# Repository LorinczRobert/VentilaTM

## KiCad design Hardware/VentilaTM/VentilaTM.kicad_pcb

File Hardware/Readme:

Still a work in progress, please review

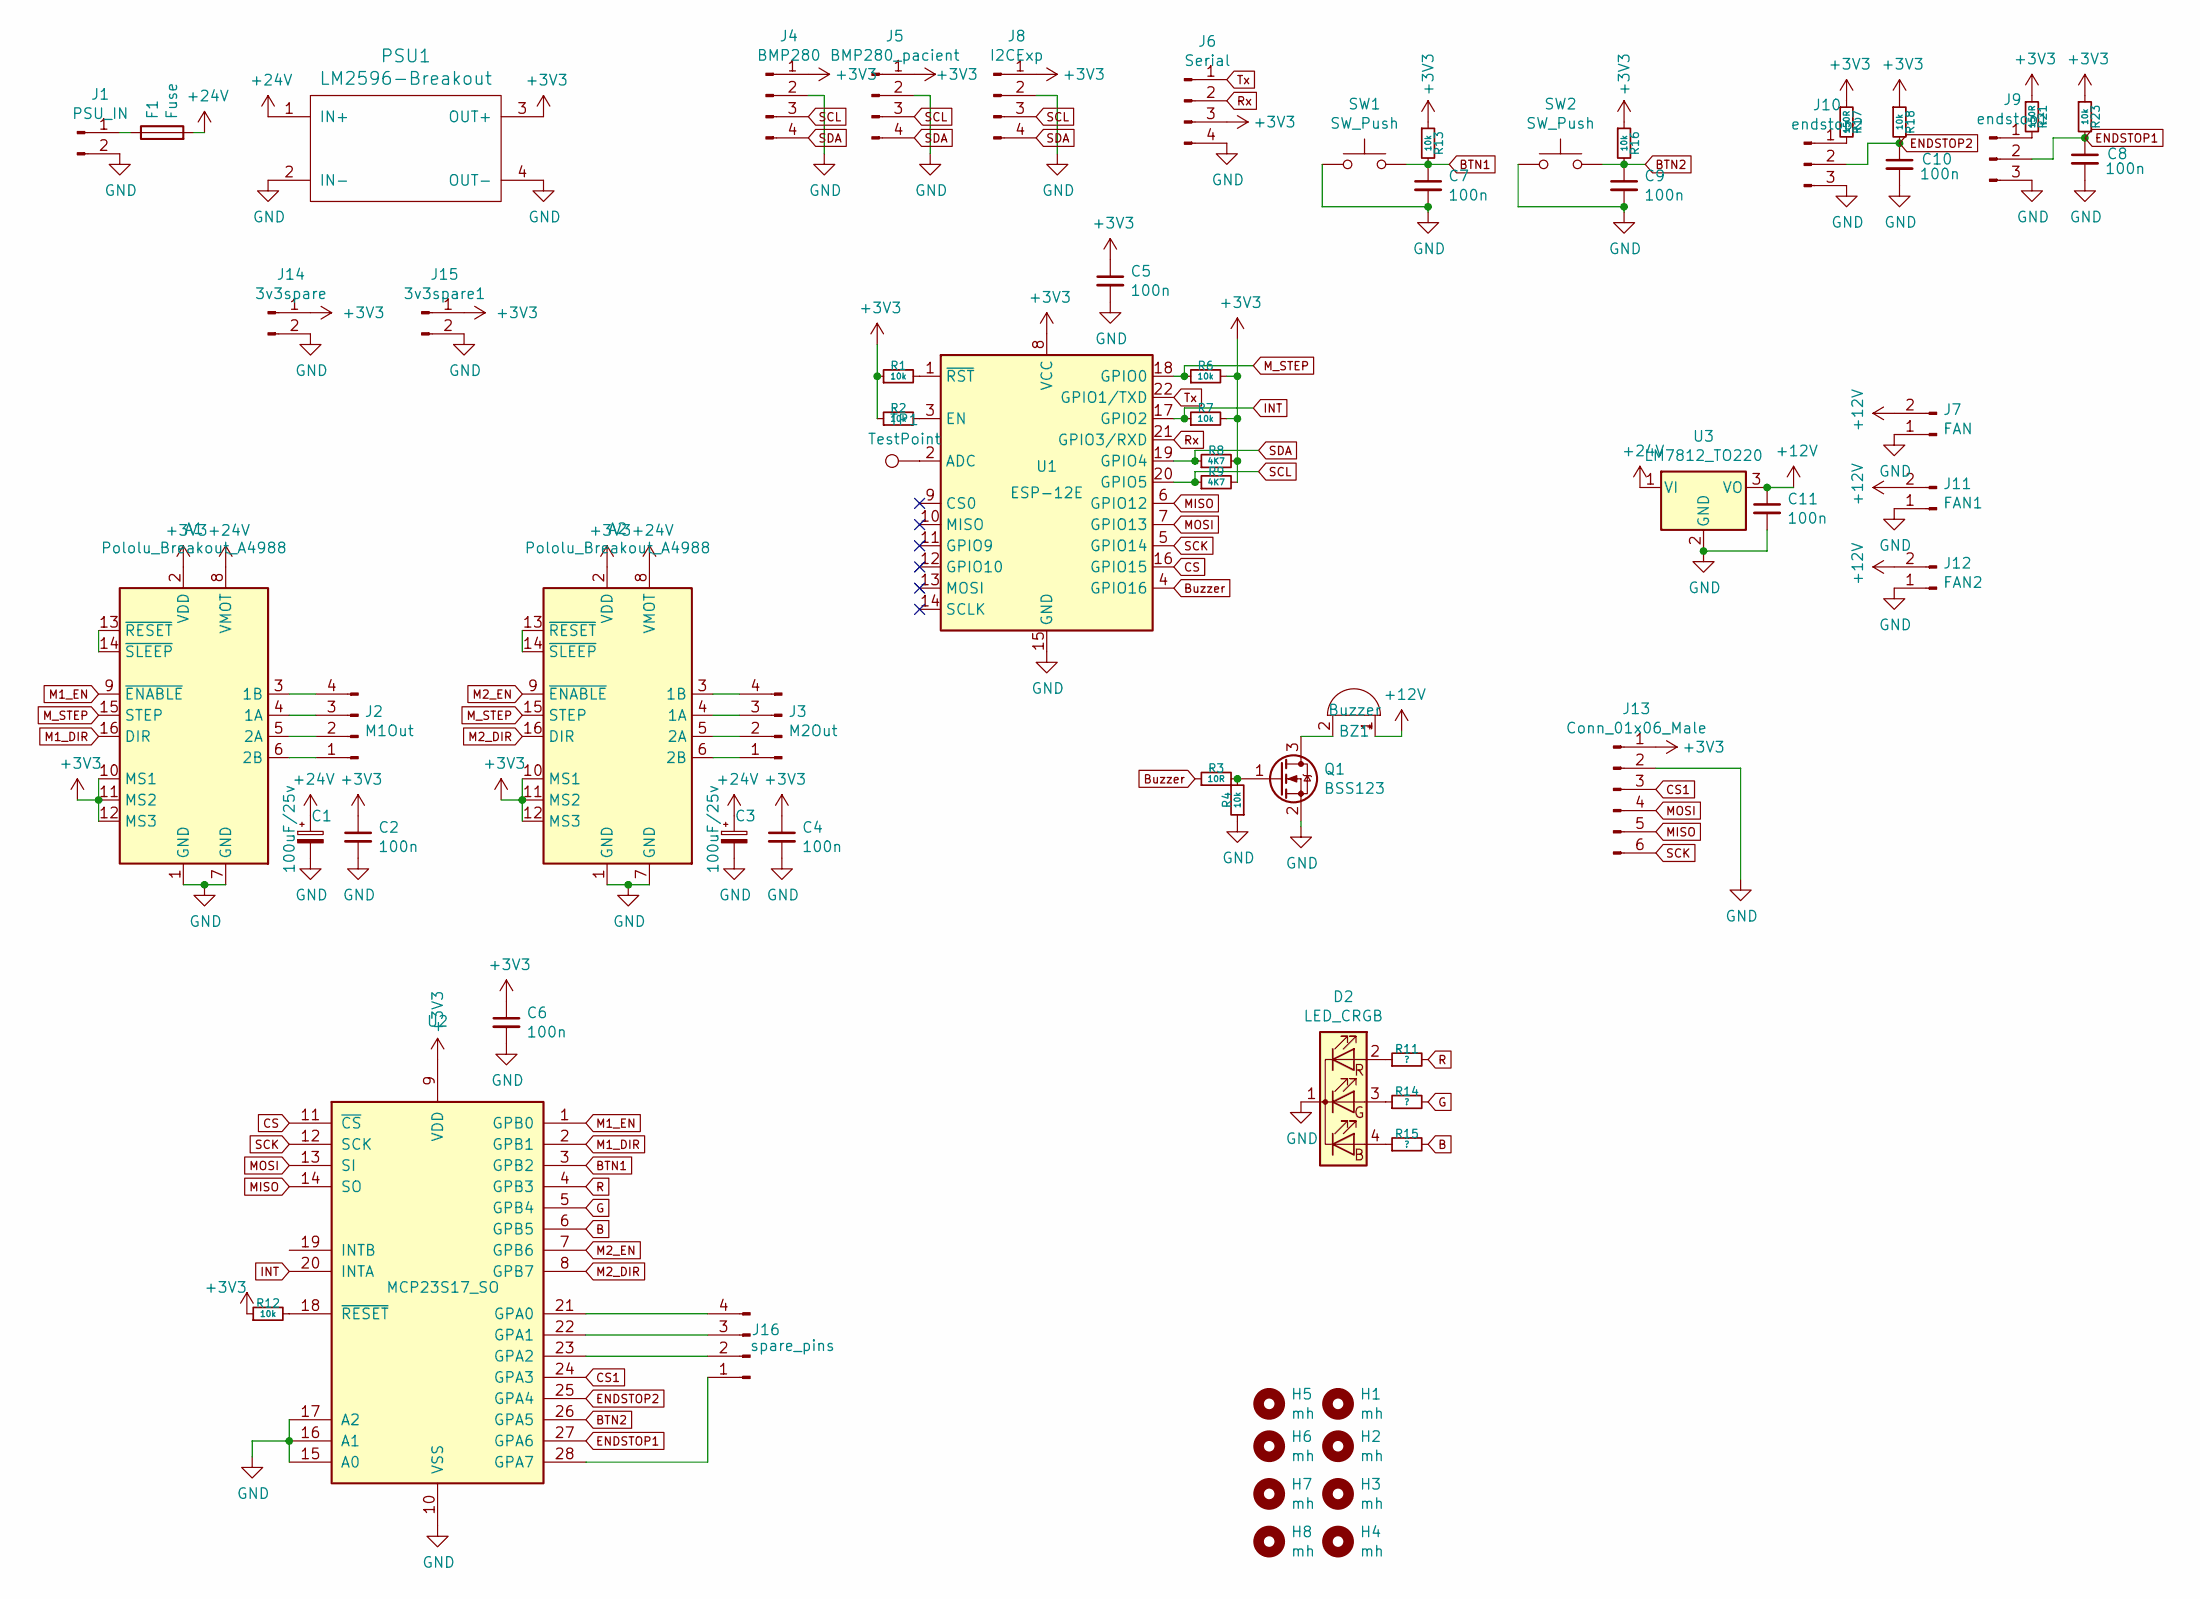
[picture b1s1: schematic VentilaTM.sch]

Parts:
A1, A2: Pololu_Breakout_A4988; Pololu_Breakout-16_15.2x20.3mm
BZ1: Buzzer; Buzzer_12x9.5RM7.6
C1, C3: 100uF/25v; CP_Elec_6.3x7.7
C2, C4, C5, C6, C7, C8, C9, C10, C11: 100n; C_0805_2012Metric_Pad1.15x1.40mm_HandSolder
D2: LED_CRGB; LED_D5.0mm-4_RGB_Wide_Pins
F1: Fuse; Fuse_BelFuse_0ZRE0100FF_L18.7mm_W5.1mm
H1, H2, H3, H4, H5, H6, H7, H8: mh; MountingHole_3.2mm_M3
J1: PSU_IN; TerminalBlock_bornier-2_P5.08mm
J2: M1Out; PinHeader_1x04_P2.54mm_Vertical
J3: M2Out; PinHeader_1x04_P2.54mm_Vertical
J4: BMP280; PinHeader_1x04_P2.54mm_Vertical
J5: BMP280_pacient; PinHeader_1x04_P2.54mm_Vertical
J6: Serial; PinHeader_1x04_P2.54mm_Vertical
J7: FAN; PinHeader_1x02_P2.54mm_Vertical
J8: I2CExp; PinHeader_1x04_P2.54mm_Vertical
J9: endstop1; PinHeader_1x03_P2.54mm_Vertical
J10: endstop2; PinHeader_1x03_P2.54mm_Vertical
J11: FAN1; PinHeader_1x02_P2.54mm_Vertical
J12: FAN2; PinHeader_1x02_P2.54mm_Vertical
J13: Conn_01x06_Male; PinHeader_1x06_P2.54mm_Vertical
J14: 3v3spare; PinHeader_1x02_P2.54mm_Vertical
J15: 3v3spare1; PinHeader_1x02_P2.54mm_Vertical
J16: spare_pins; PinHeader_1x04_P2.54mm_Vertical
PSU1: LM2596-Breakout; LM2596-breakout_board
Q1: BSS123; SOT-23
R1, R2, R4, R6, R7, R12, R13, R16, R18, R23: 10k; R_0805_2012Metric_Pad1.15x1.40mm_HandSolder
R3: 10R; R_0805_2012Metric_Pad1.15x1.40mm_HandSolder
R8, R9: 4K7; R_0805_2012Metric_Pad1.15x1.40mm_HandSolder
R11, R14, R15: ?; R_0805_2012Metric_Pad1.15x1.40mm_HandSolder
R17, R21: 150R; R_0805_2012Metric_Pad1.15x1.40mm_HandSolder
SW1, SW2: SW_Push; SW_PUSH_6mm_H7.3mm
TP1: TestPoint; TestPoint_Pad_D1.5mm
U1: ESP-12E
U2: MCP23S17_SO; SOIC-28W_7.5x17.9mm_P1.27mm
U3: LM7812_TO220; TO-220-3_Horizontal_TabUp

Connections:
+3V3: A1.2 (VDD), A1.10 (MS1), A1.11 (MS2), A1.12 (MS3), A2.2 (VDD), A2.10 (MS1), A2.11 (MS2), A2.12 (MS3), C2.1, C4.1, C5.1, C6.1, J4.1, J5.1, J6.3, J8.1, J13.1, J14.1, J15.1, PSU1.3 (OUT+), R1.1, R2.1, R6.2, R7.2, R8.2, R9.2, R12.1, R13.1, R16.1, R17.1, R18.1, R21.1, R23.1, U1.8 (VCC), U2.9 (VDD)
+12V: BZ1.1 (-), C11.1, J7.2, J11.2, J12.2, U3.3 (VO)
+24V: A1.8 (VMOT), A2.8 (VMOT), C1.1, C3.1, F1.2, PSU1.1 (IN+), U3.1 (VI)
B: R15.2, U2.6 (GPB5)
BTN1: C7.1, R13.2, SW1.2, U2.3 (GPB2)
BTN2: C9.1, R16.2, SW2.2, U2.26 (GPA5)
Buzzer: R3.1, U1.4 (GPIO16)
CS: U1.16 (GPIO15), U2.11 (~CS~)
CS1: J13.3, U2.24 (GPA3)
ENDSTOP1: C8.1, J9.2, R23.2, U2.27 (GPA6)
ENDSTOP2: C10.1, J10.2, R18.2, U2.25 (GPA4)
G: R14.2, U2.5 (GPB4)
GND: A1.1 (GND), A1.7 (GND), A2.1 (GND), A2.7 (GND), C1.2, C2.2, C3.2, C4.2, C5.2, C6.2, C7.2, C8.2, C9.2, C10.2, C11.2, D2.1 (K), J1.2, J4.2, J5.2, J6.4, J7.1, J8.2, J9.3, J10.3, J11.1, J12.1, J13.2, J14.2, J15.2, PSU1.2 (IN-), PSU1.4 (OUT-), Q1.2 (S), R4.1, SW1.1, SW2.1, U1.15 (GND), U2.10 (VSS), U2.15 (A0), U2.16 (A1), U2.17 (A2), U3.2 (GND)
INT: R7.1, U1.17 (GPIO2), U2.20 (INTA)
M1_DIR: A1.16 (DIR), U2.2 (GPB1)
M1_EN: A1.9 (~ENABLE), U2.1 (GPB0)
M2_DIR: A2.16 (DIR), U2.8 (GPB7)
M2_EN: A2.9 (~ENABLE), U2.7 (GPB6)
MISO: J13.5, U1.6 (GPIO12), U2.14 (SO)
MOSI: J13.4, U1.7 (GPIO13), U2.13 (SI)
M_STEP: A1.15 (STEP), A2.15 (STEP), R6.1, U1.18 (GPIO0)
unnamed: A1.3 (1B), J2.4
unnamed: A1.4 (1A), J2.3
unnamed: A1.5 (2A), J2.2
unnamed: A1.6 (2B), J2.1
unnamed: A1.13 (~RESET), A1.14 (~SLEEP)
unnamed: A2.3 (1B), J3.4
unnamed: A2.4 (1A), J3.3
unnamed: A2.5 (2A), J3.2
unnamed: A2.6 (2B), J3.1
unnamed: A2.13 (~RESET), A2.14 (~SLEEP)
unnamed: BZ1.2 (+), Q1.3 (D)
unnamed: D2.2 (RA), R11.1
unnamed: D2.3 (GA), R14.1
unnamed: D2.4 (BA), R15.1
unnamed: F1.1, J1.1
unnamed: J9.1, R21.2
unnamed: J10.1, R17.2
unnamed: J16.1, U2.28 (GPA7)
unnamed: J16.2, U2.23 (GPA2)
unnamed: J16.3, U2.22 (GPA1)
unnamed: J16.4, U2.21 (GPA0)
unnamed: Q1.1 (G), R3.2, R4.2
unnamed: R1.2, U1.1 (~RST)
unnamed: R2.2, U1.3 (EN)
unnamed: R12.2, U2.18 (~RESET~)
unnamed: TP1.1, U1.2 (ADC)
R: R11.2, U2.4 (GPB3)
Rx: J6.2, U1.21 (GPIO3/RXD)
SCK: J13.6, U1.5 (GPIO14), U2.12 (SCK)
SCL: J4.3, J5.3, J8.3, R9.1, U1.20 (GPIO5)
SDA: J4.4, J5.4, J8.4, R8.1, U1.19 (GPIO4)
Tx: J6.1, U1.22 (GPIO1/TXD)

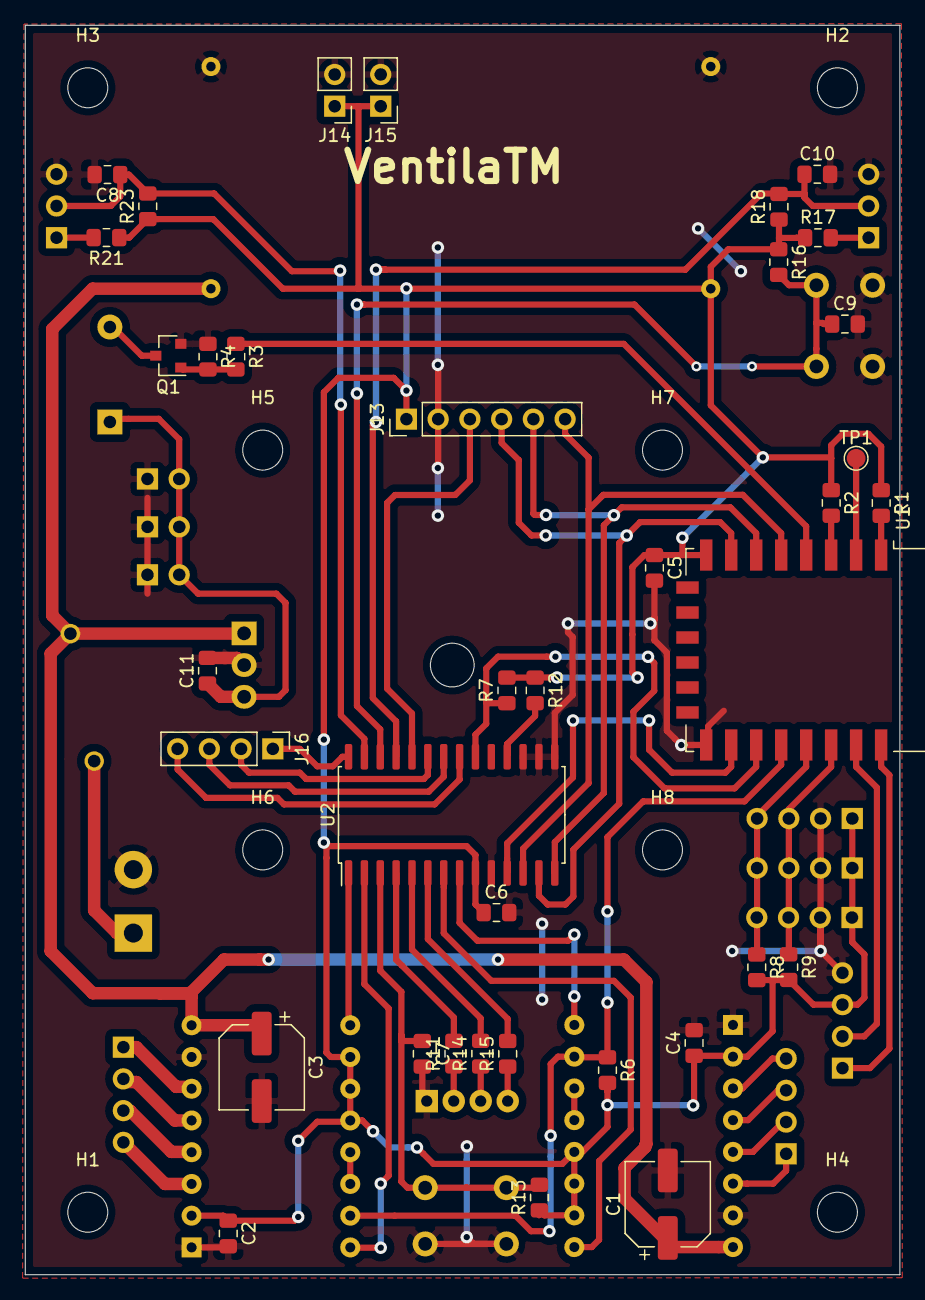
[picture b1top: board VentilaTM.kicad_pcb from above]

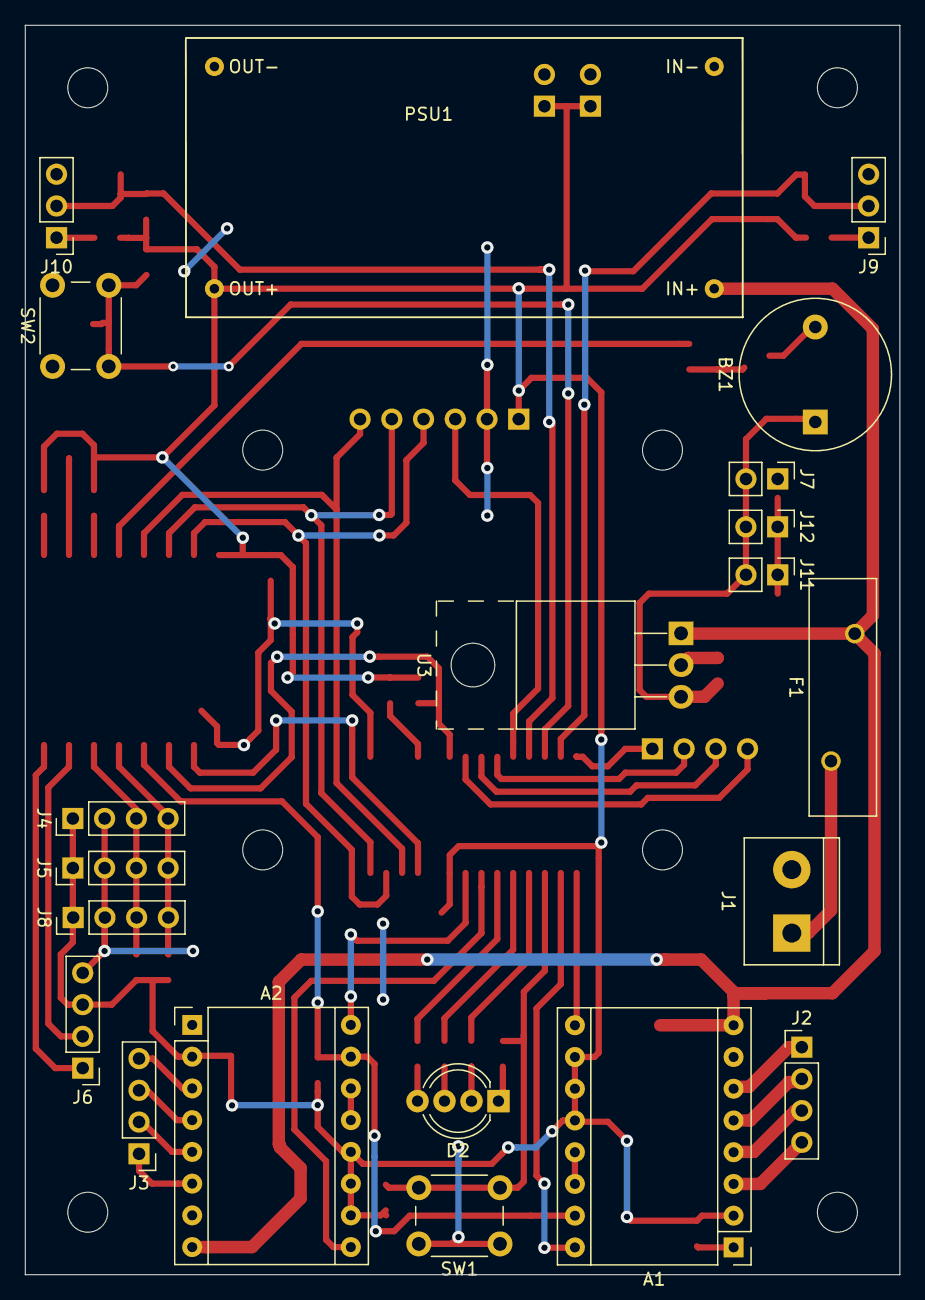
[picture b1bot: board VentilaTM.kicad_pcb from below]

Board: 2 copper layers, 70.0 x 100.0 mm, 66 parts (21 on the bottom side), 53 nets.

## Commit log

2020-03-23 Added Kicad project
2020-03-24 update
    fixed some issues, still W-I-P
